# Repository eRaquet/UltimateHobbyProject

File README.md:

# The Ultimate Hobby Project

This code is released under the MIT licence.

### Project Description

This is the firmware for a self-balancing two-wheeled robot.
The robot uses stepper motors for transport, an LQG controller for stability, and a Kalman filter for sensor filtering.
This project has been a great way for me to develop practical skills in many different areas.  If you would like to see a technical write-up of this project, you can find it [here](https://drive.google.com/file/d/1yd39i1YjvD11JdsaPKPIDzlGQhWOL76k/view?usp=drive_link).

I hope that this repo will encourage you to try to conquer the inverted pendulum as I have. :)

### Requirements

This project utilizes a [Nano 33 BLE](https://docs.arduino.cc/hardware/nano-33-ble) as its processor core and the [A4988](https://www.digikey.com/en/htmldatasheets/production/693406/0/0/1/a4988) motor driver to drive the [stepper motors](https://www.amazon.com/Usongshine-Nema17-Stepper-17HS4401S-Printer/dp/B0787BQ4WH/ref=asc_df_B07KW6B3ZX?tag=bingshoppinga-20&linkCode=df0&hvadid=80333123589250&hvnetw=o&hvqmt=e&hvbmt=be&hvdev=c&hvlocint=&hvlocphy=&hvtargid=pla-4583932701264073&th=1).  For power, it uses a [TalentCell YB1203000](https://www.talentcell.com/lithium-ion-battery/12v/yb1203000-usb.html) Lithium Ion battery.

On the software side, the code requires two arduino libraries: <BasicLinearAlgibra.h> and <Arduino_LSM9DS1.h>.  I couldn't find a good way to calculate the controller gain on the arduino board, so I used the Scipy and Numpy libraries in Python to [calculate](./Code/findControlGain.py) the controller and copied the values into the [arduino code](./Code/robotCode.ino).

Enjoy!!!

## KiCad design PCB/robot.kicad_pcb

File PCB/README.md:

# The PCB

This folder contains the files regarding the robot's Curcuit Board.  I designed the board in [Kicad](https://www.kicad.org/) and had it manufactured by [JLCPCB](https://jlcpcb.com/).  I bought the sockets and powerjack on [Digikey](https://www.digikey.com/).  If you make changes to the board layout or design, you will have to change the [3D print files](../PrintFiles).

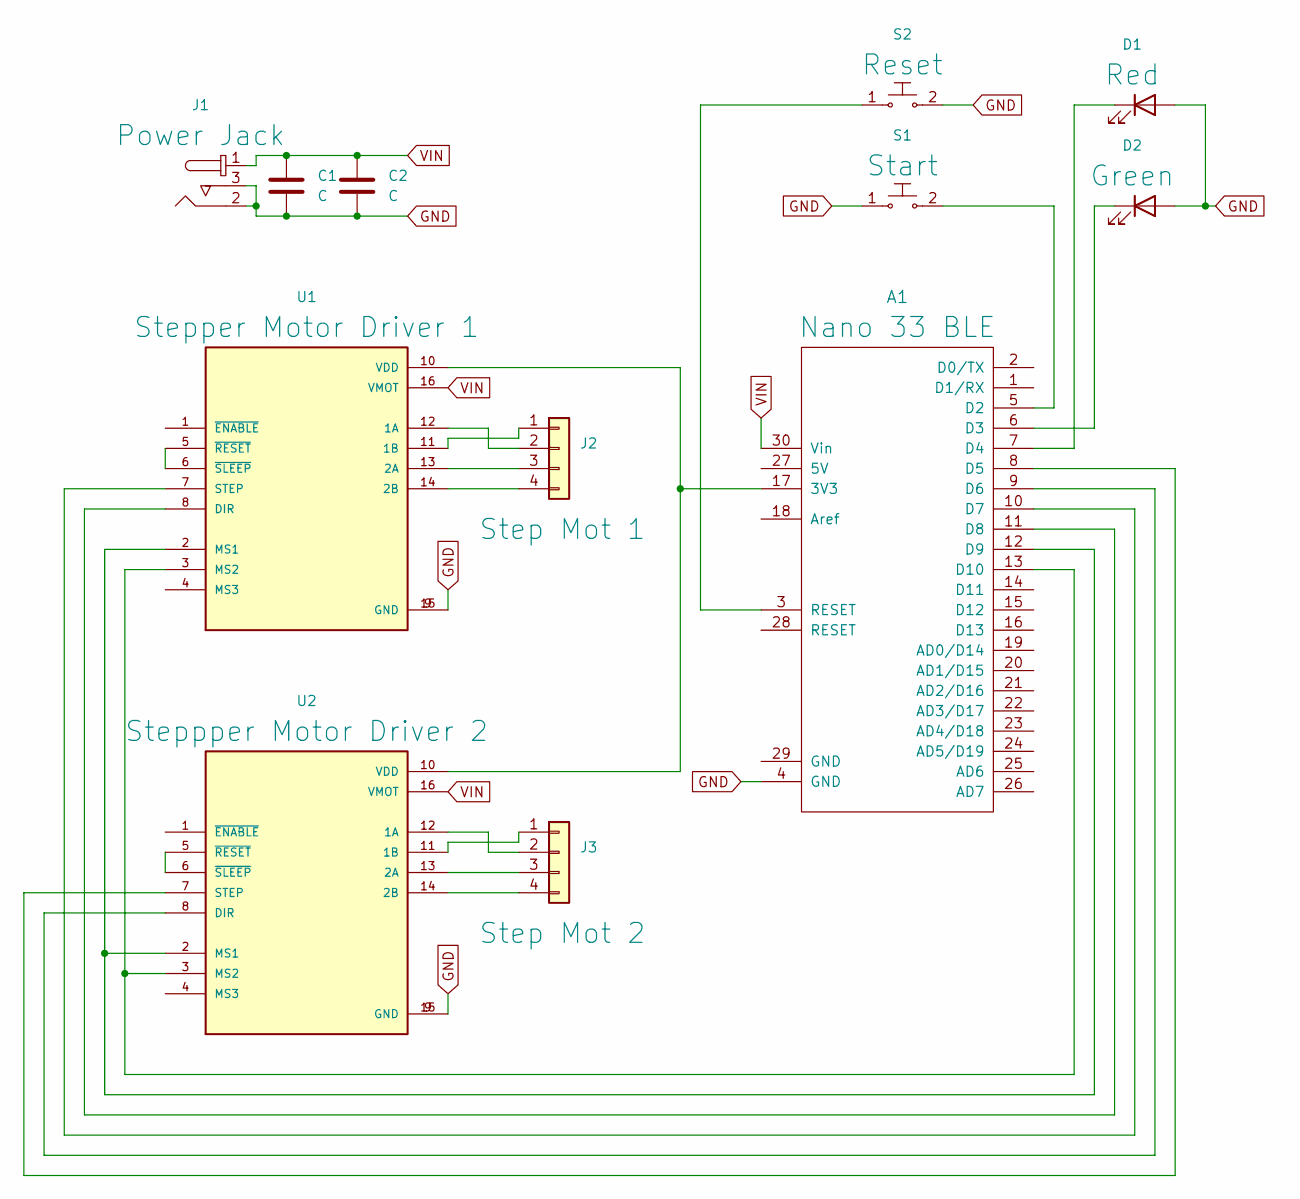
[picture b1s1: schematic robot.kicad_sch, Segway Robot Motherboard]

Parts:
A1: Nano 33 BLE; arduino_nano
C1, C2: C; C_Radial_D5.0mm_H11.0mm_P2.00mm
D1: Red; LED_D3.0mm
D2: Green; LED_D3.0mm
J1: Power Jack; Barrel_Jack_5.5mmODx2.1mmID_PJ-202A; MPN PJ-202A; Digi-Key_PN CP-202A-ND
J2: Step Mot 1; PinHeader_1x04_P2.54mm_Vertical
J3: Step Mot 2; PinHeader_1x04_P2.54mm_Vertical
S1: Start; SW_PUSH_6mm; MPN GPTS203211B; Digi-Key_PN CW181-ND
S2: Reset; SW_PUSH_6mm; MPN GPTS203211B; Digi-Key_PN CW181-ND
U1: Stepper Motor Driver 1; MODULE_A4988_STEPPER_MOTOR_DRIVER_CARRIER
U2: Steppper Motor Driver 2; MODULE_A4988_STEPPER_MOTOR_DRIVER_CARRIER

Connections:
GND: A1.4 (GND), C1.2, C2.2, D1.2 (A), D2.2 (A), J1.2, J1.3, S1.1, S2.2, U1.9 (GND), U1.15 (GND), U2.9 (GND), U2.15 (GND)
unnamed: A1.3 (RESET), S2.1
unnamed: A1.6 (D3), D2.1 (K)
unnamed: A1.7 (D4), D1.1 (K)
unnamed: A1.17 (3V3), U1.10 (VDD), U2.10 (VDD)
unnamed: J2.1, U1.11 (1B)
unnamed: J2.2, U1.12 (1A)
unnamed: J2.3, U1.13 (2A)
unnamed: J2.4, U1.14 (2B)
unnamed: J3.1, U2.11 (1B)
unnamed: J3.2, U2.12 (1A)
unnamed: J3.3, U2.13 (2A)
unnamed: J3.4, U2.14 (2B)
unnamed: A1.5 (D2), S1.2
unnamed: A1.12 (D9), U1.2 (MS1), U2.2 (MS1)
unnamed: A1.13 (D10), U1.3 (MS2), U2.3 (MS2)
unnamed: U1.5 (~RESET), U1.6 (~SLEEP)
unnamed: A1.10 (D7), U1.7 (STEP)
unnamed: A1.11 (D8), U1.8 (DIR)
unnamed: U2.5 (~RESET), U2.6 (~SLEEP)
unnamed: A1.8 (D5), U2.7 (STEP)
unnamed: A1.9 (D6), U2.8 (DIR)
VIN: A1.30 (Vin), C1.1, C2.1, J1.1, U1.16 (VMOT), U2.16 (VMOT)

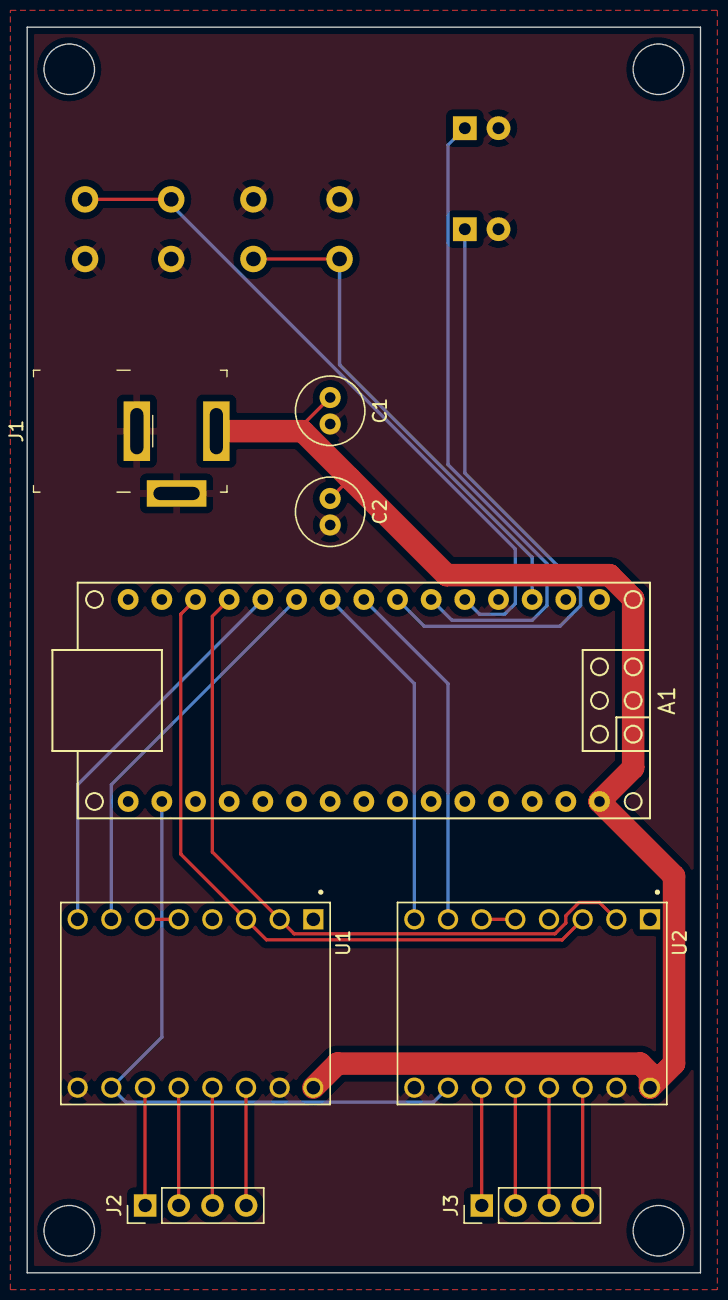
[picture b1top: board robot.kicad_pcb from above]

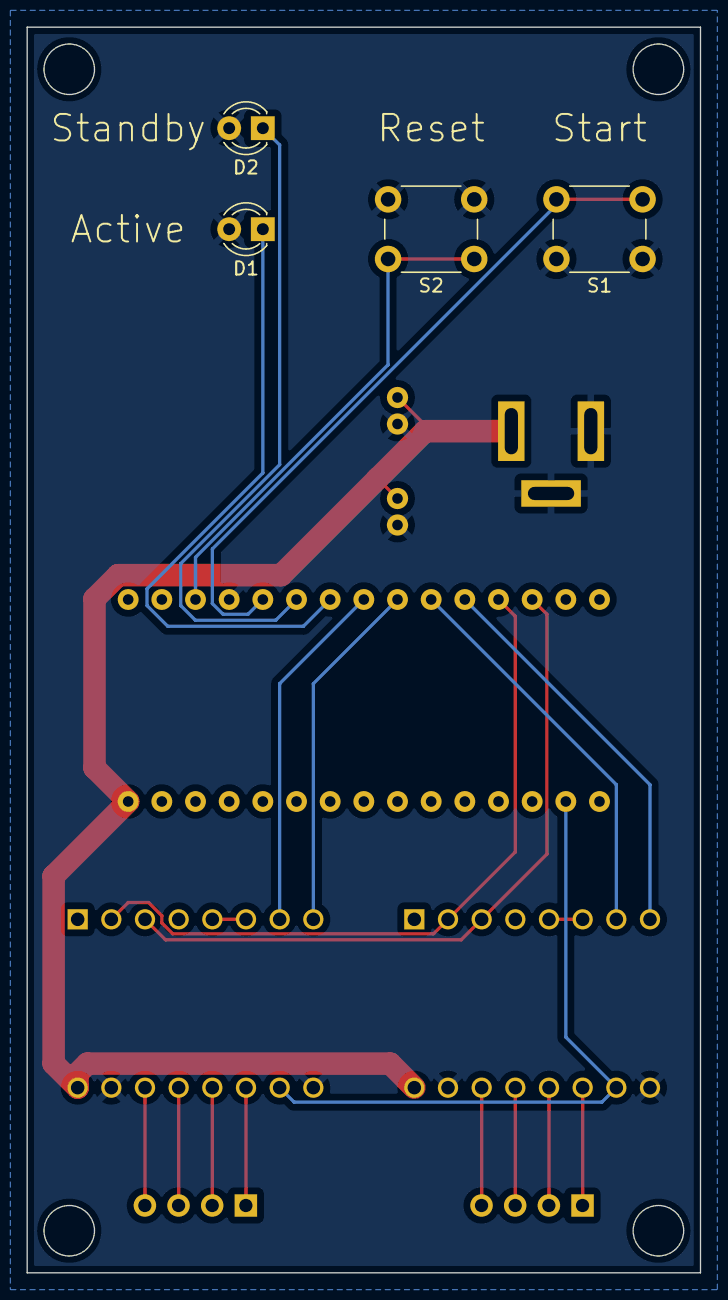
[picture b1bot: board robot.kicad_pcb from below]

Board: 2 copper layers, 50.8 x 94.0 mm, 12 parts (4 on the bottom side), 23 nets.

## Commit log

2023-07-12 Initial
